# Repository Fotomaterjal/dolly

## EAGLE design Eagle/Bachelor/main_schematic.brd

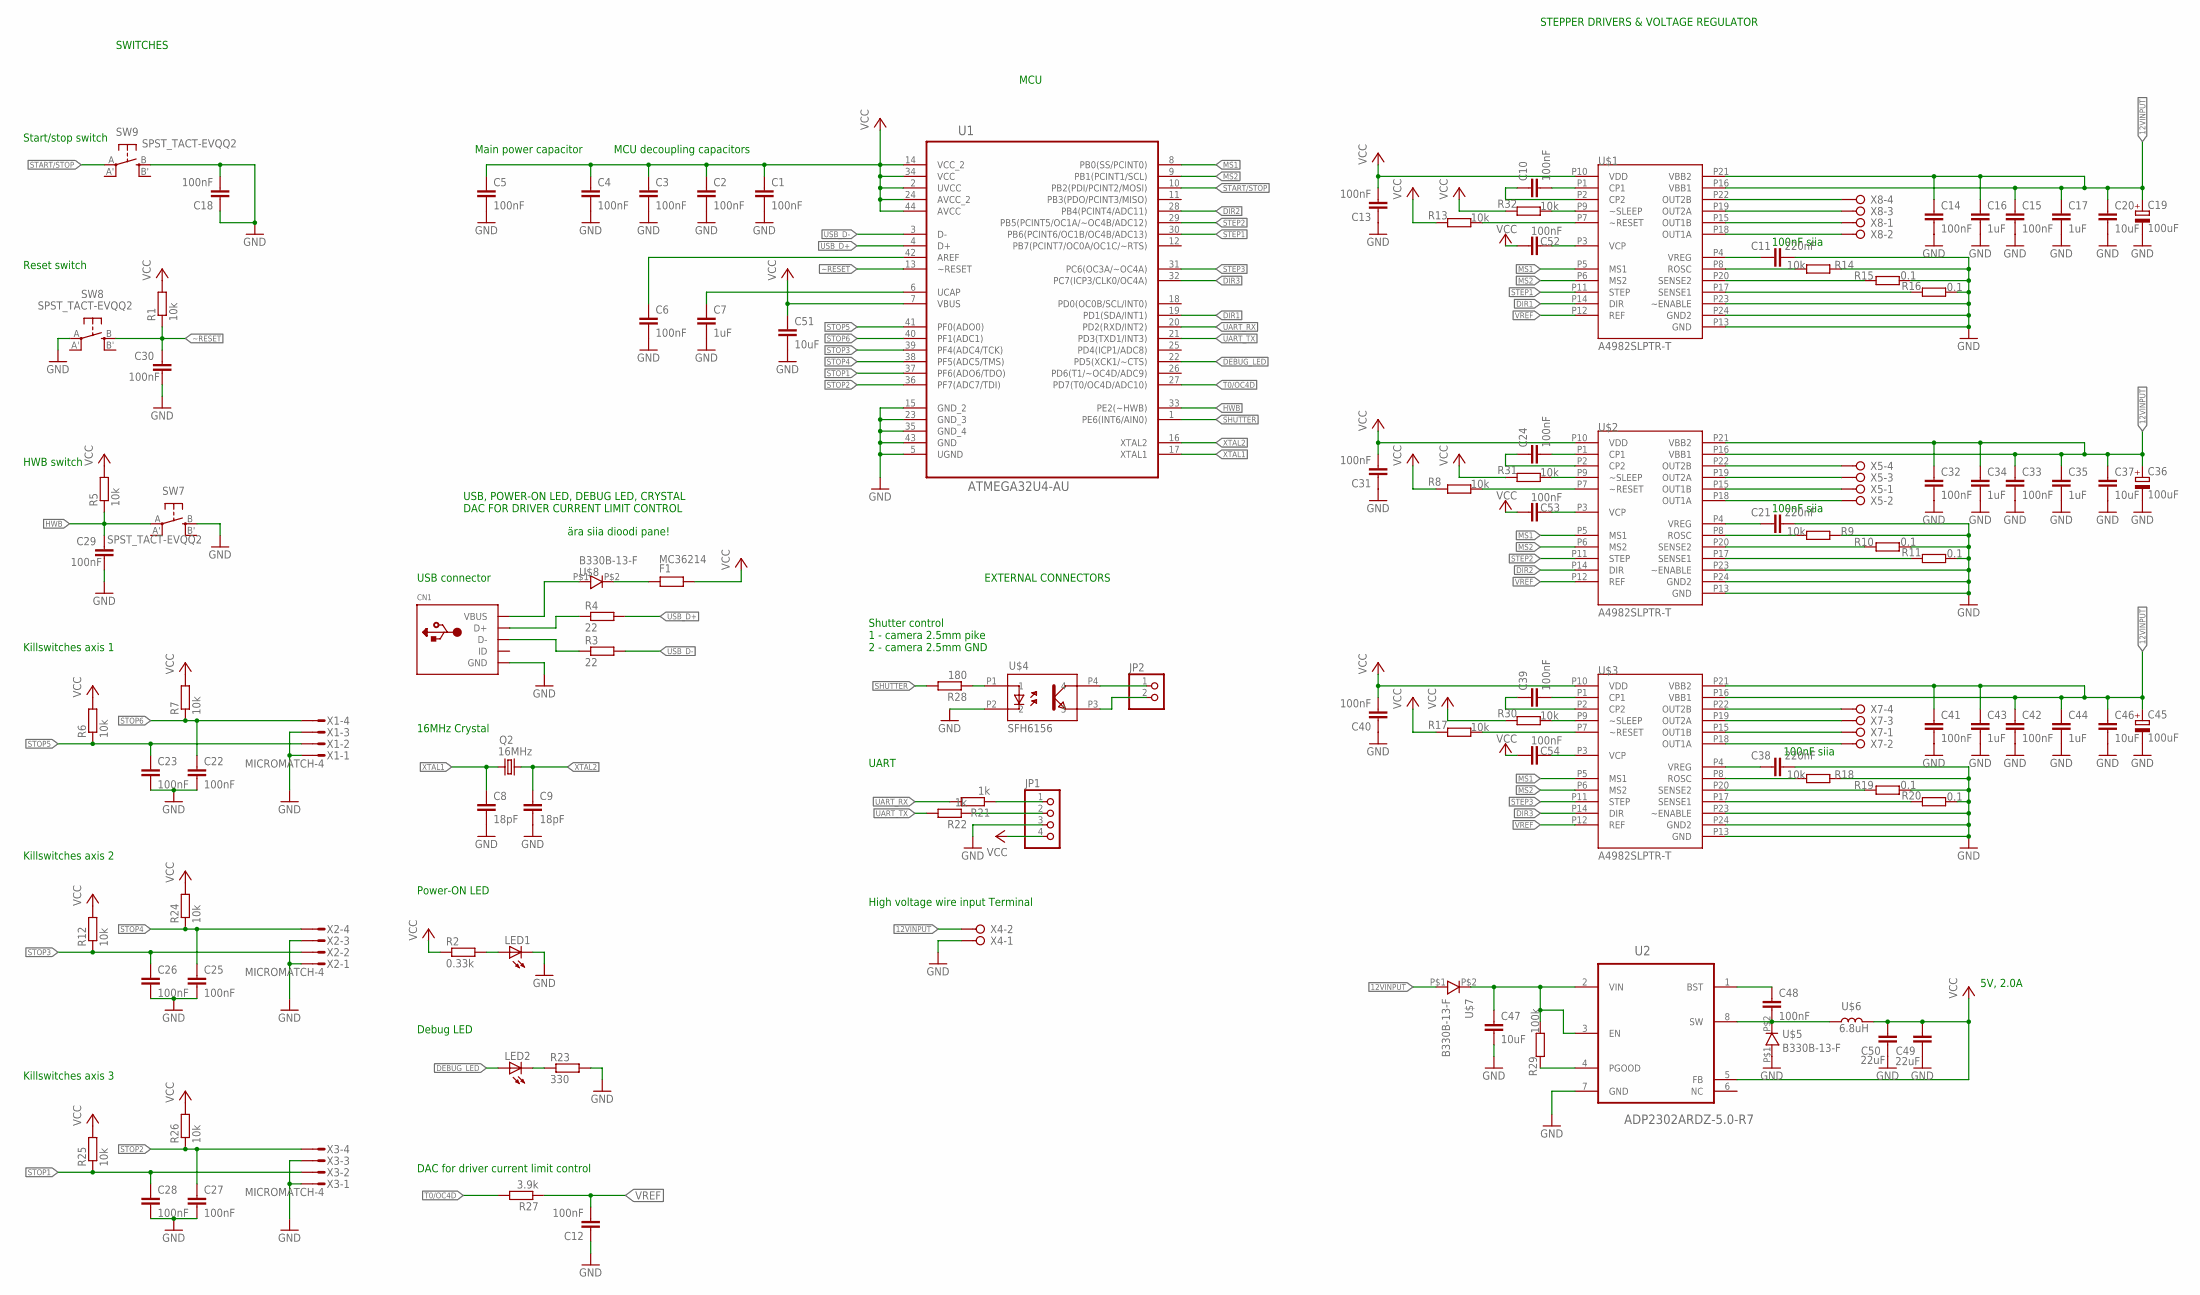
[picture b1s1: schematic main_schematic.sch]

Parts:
C1, C2, C3, C4, C5, C6, C10, C12, C13, C14, C15, C18, C22, C23, C24, C25, C26, C27, C28, C29, C30, C31, C32, C33, C39, C40, C41, C42, C52, C53, C54: 100nF; C0603K
C7, C16, C17, C34, C35, C43, C44: 1uF; C0603K
C8, C9: 18pF; C0603K
C11, C21, C38: 220nF; C0603K
C19, C36, C45: 100uF; E/7260-38R
C20, C37, C46, C47: 10uF; C1206K
C48: 100nF; C1206K
C49, C50: 22uF; C1206K
C51: 10uF; C0805
CN1: USBMINIB; USB-MINIB
F1: MC36214
JP1: PINHD-1X4; 1X04
JP2: PINHD-1X2; 1X02
LED1, LED2: LEDCHIP-LED0603; CHIP-LED0603
Q2: 16MHz; SM49
R1, R5, R6, R7, R8, R9, R12, R13, R14, R17, R18, R24, R25, R26, R30, R31, R32: 10k; R0603
R2: 0.33k; R0603
R3, R4: 22; R0603
R10, R11, R15, R16, R19, R20: 0.1; R0805
R21, R22: 1k; R0603
R23: 330; R0603
R27: 3.9k; R0603
R28: 180; R0603
R29: 100k; R0603
SW7, SW8, SW9: SPST_TACT-EVQQ2; EVQ-Q2
U1: ATMEGA32U4-AU; QFP80P1200X1200X120-44N
U2: ADP2302ARDZ-5.0-R7; SOIC127P600X175-9N
U$1, U$2, U$3: A4982SLPTR-T; TSSOP_24
U$4: SFH6156; SFH6165
U$5, U$7, U$8: B330B-13-F
U$6: 6.8uH; VLF10040
X1, X2, X3: MICROMATCH-4
X4: W237-02P; W237-132
X5, X7, X8: W237-04P; W237-4P

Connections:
12VINPUT: C14.1, C15.1, C16.1, C17.1, C19.+, C20.1, C32.1, C33.1, C34.1, C35.1, C36.+, C37.1, C41.1, C42.1, C43.1, C44.1, C45.+, C46.1, U$1.P16 (VBB1), U$1.P21 (VBB2), U$2.P16 (VBB1), U$2.P21 (VBB2), U$3.P16 (VBB1), U$3.P21 (VBB2), U$7.P$1, X4.2
DEBUG_LED: LED2.A, U1.22 (PD5(XCK1/~CTS))
DIR1: U1.19 (PD1(SDA/INT1)), U$1.P14 (DIR)
DIR2: U1.28 (PB4(PCINT4/ADC11)), U$2.P14 (DIR)
DIR3: U1.32 (PC7(ICP3/CLK0/OC4A)), U$3.P14 (DIR)
GND: C1.2, C2.2, C3.2, C4.2, C5.2, C6.2, C7.2, C8.2, C9.2, C11.1, C12.1, C13.1, C14.2, C15.2, C16.2, C17.2, C18.1, C18.2, C19.-, C20.2, C21.1, C22.2, C23.2, C25.2, C26.2, C27.2, C28.2, C29.2, C30.2, C31.1, C32.2, C33.2, C34.2, C35.2, C36.-, C37.2, C38.1, C40.1, C41.2, C42.2, C43.2, C44.2, C45.-, C46.2, C47.2, C49.1, C50.1, C51.2, CN1.GND, JP1.3, LED1.C, R9.1, R10.2, R11.2, R14.1, R15.2, R16.2, R18.1, R19.2, R20.2, R23.2, SW7.B (S), SW8.A, SW9.B (S), U1.5 (UGND), U1.15 (GND_2), U1.23 (GND_3), U1.35 (GND_4), U1.43 (GND), U2.7 (GND), U$1.P13 (GND), U$1.P23 (~ENABLE), U$1.P24 (GND2), U$2.P13 (GND), U$2.P23 (~ENABLE), U$2.P24 (GND2), U$3.P13 (GND), U$3.P23 (~ENABLE), U$3.P24 (GND2), U$4.P2 (2), U$5.P$1, X1.1, X1.3, X2.1, X2.3, X3.1, X3.3, X4.1
HIGH_VOLTAEG: C47.1, R29.2, U2.2 (VIN), U2.3 (EN), U$7.P$2
HWB: C29.1, R5.1, SW7.A, U1.33 (PE2(~HWB))
MS1: U1.8 (PB0(SS/PCINT0)), U$1.P5 (MS1), U$2.P5 (MS1), U$3.P5 (MS1)
MS2: U1.9 (PB1(PCINT1/SCL)), U$1.P6 (MS2), U$2.P6 (MS2), U$3.P6 (MS2)
unnamed: JP2.1, U$4.P4 (4)
unnamed: C6.1, U1.42 (AREF)
unnamed: LED1.A, R2.2
unnamed: CN1.D-, R3.1
unnamed: CN1.D+, R4.1
unnamed: C10.2, U$1.P1 (CP1)
unnamed: C10.1, U$1.P2 (CP2)
unnamed: U$1.P15 (OUT1B), X8.1
unnamed: U$1.P22 (OUT2B), X8.4
unnamed: C11.2, U$1.P4 (VREG)
unnamed: C7.1, U1.6 (UCAP)
unnamed: R13.2, U$1.P7 (~RESET)
unnamed: C24.2, U$2.P1 (CP1)
unnamed: R14.2, U$1.P8 (ROSC)
unnamed: R15.1, U$1.P20 (SENSE2)
unnamed: R16.1, U$1.P17 (SENSE1)
unnamed: C24.1, U$2.P2 (CP2)
unnamed: U$1.P19 (OUT2A), X8.3
unnamed: R10.1, U$2.P20 (SENSE2)
unnamed: U$1.P18 (OUT1A), X8.2
unnamed: R11.1, U$2.P17 (SENSE1)
unnamed: U$2.P22 (OUT2B), X5.4
unnamed: U$2.P15 (OUT1B), X5.1
unnamed: U$2.P19 (OUT2A), X5.3
unnamed: U$2.P18 (OUT1A), X5.2
unnamed: C21.2, U$2.P4 (VREG)
unnamed: R8.2, U$2.P7 (~RESET)
unnamed: R9.2, U$2.P8 (ROSC)
unnamed: C39.2, U$3.P1 (CP1)
unnamed: C39.1, U$3.P2 (CP2)
unnamed: R19.1, U$3.P20 (SENSE2)
unnamed: R20.1, U$3.P17 (SENSE1)
unnamed: U$3.P22 (OUT2B), X7.4
unnamed: U$3.P15 (OUT1B), X7.1
unnamed: U$3.P19 (OUT2A), X7.3
unnamed: U$3.P18 (OUT1A), X7.2
unnamed: C38.2, U$3.P4 (VREG)
unnamed: R17.2, U$3.P7 (~RESET)
unnamed: CN1.VBUS, U$8.P$1
unnamed: JP1.1, R21.1
unnamed: JP1.2, R22.1
unnamed: JP2.2, U$4.P3 (3)
unnamed: R18.2, U$3.P8 (ROSC)
unnamed: LED2.C, R23.1
unnamed: R29.1, U2.4 (PGOOD)
unnamed: C48.1, U2.1 (BST)
unnamed: R28.1, U$4.P1 (1)
unnamed: F1.P$1, U$8.P$2
unnamed: C52.1, U$1.P3 (VCP)
unnamed: C48.2, U2.8 (SW), U$5.P$2, U$6.P$2
unnamed: C53.1, U$2.P3 (VCP)
unnamed: C54.1, U$3.P3 (VCP)
unnamed: R30.2, U$3.P9 (~SLEEP)
unnamed: R31.2, U$2.P9 (~SLEEP)
unnamed: R32.2, U$1.P9 (~SLEEP)
SHUTTER: R28.2, U1.1 (PE6(INT6/AIN0))
START/STOP: SW9.A, U1.10 (PB2(PDI/PCINT2/MOSI))
STEP1: U1.30 (PB6(PCINT6/OC1B/OC4B/ADC13)), U$1.P11 (STEP)
STEP2: U1.29 (PB5(PCINT5/OC1A/~OC4B/ADC12)), U$2.P11 (STEP)
STEP3: U1.31 (PC6(OC3A/~OC4A)), U$3.P11 (STEP)
STOP1: C28.1, R25.1, U1.37 (PF6(ADO6/TDO)), X3.2
STOP2: C27.1, R26.1, U1.36 (PF7(ADC7/TDI)), X3.4
STOP3: C26.1, R12.1, U1.39 (PF4(ADC4/TCK)), X2.2
STOP4: C25.1, R24.1, U1.38 (PF5(ADC5/TMS)), X2.4
STOP5: C23.1, R6.1, U1.41 (PF0(ADO0)), X1.2
STOP6: C22.1, R7.1, U1.40 (PF1(ADC1)), X1.4
T0/OC4D: R27.2, U1.27 (PD7(T0/OC4D/ADC10))
UART_RX: R21.2, U1.20 (PD2(RXD/INT2))
UART_TX: R22.2, U1.21 (PD3(TXD1/INT3))
USB_D+: R4.2, U1.4 (D+)
USB_D-: R3.2, U1.3 (D-)
VCC: C1.1, C2.1, C3.1, C4.1, C5.1, C13.2, C31.2, C40.2, C49.2, C50.2, C51.1, C52.2, C53.2, C54.2, F1.P$2, JP1.4, R1.2, R2.1, R5.2, R6.2, R7.2, R8.1, R12.2, R13.1, R17.1, R24.2, R25.2, R26.2, R30.1, R31.1, R32.1, U1.2 (UVCC), U1.7 (VBUS), U1.14 (VCC_2), U1.24 (AVCC_2), U1.34 (VCC), U1.44 (AVCC), U2.5 (FB), U$1.P10 (VDD), U$2.P10 (VDD), U$3.P10 (VDD), U$6.P$1
VREF: C12.2, R27.1, U$1.P12 (REF), U$2.P12 (REF), U$3.P12 (REF)
XTAL1: C8.1, Q2.1, U1.17 (XTAL1)
XTAL2: C9.1, Q2.2, U1.16 (XTAL2)
~RESET: C30.1, R1.1, SW8.B (S), U1.13 (~RESET)

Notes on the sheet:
MCU decoupling capacitors
Main power capacitor
Reset switch
Power-ON LED
USB connector
HWB switch
Start/stop switch
Killswitches axis 1
Killswitches axis 2
Killswitches axis 3
Debug LED
16MHz Crystal
Shutter control 1 - camera 2.5mm pike 2 - camera 2.5mm GND
DAC for driver current limit control
UART
High voltage wire input Terminal
5V, 2.0A
SWITCHES
MCU
USB, POWER-ON LED, DEBUG LED, CRYSTAL DAC FOR DRIVER CURRENT LIMIT CONTROL
STEPPER DRIVERS & VOLTAGE REGULATOR
EXTERNAL CONNECTORS
ära siia dioodi pane!
100nF siia

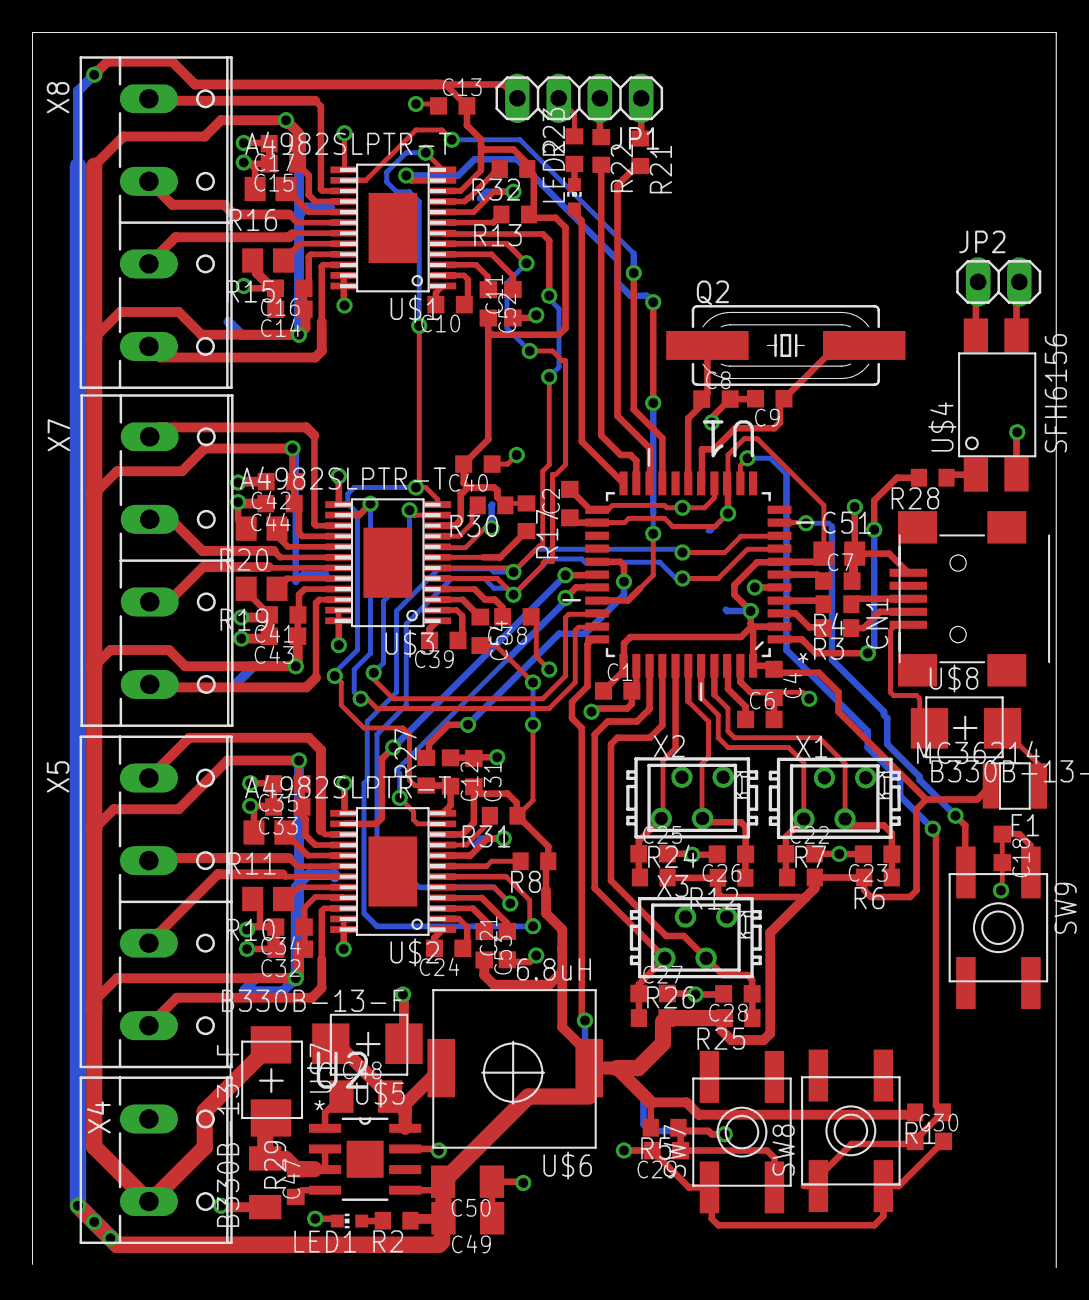
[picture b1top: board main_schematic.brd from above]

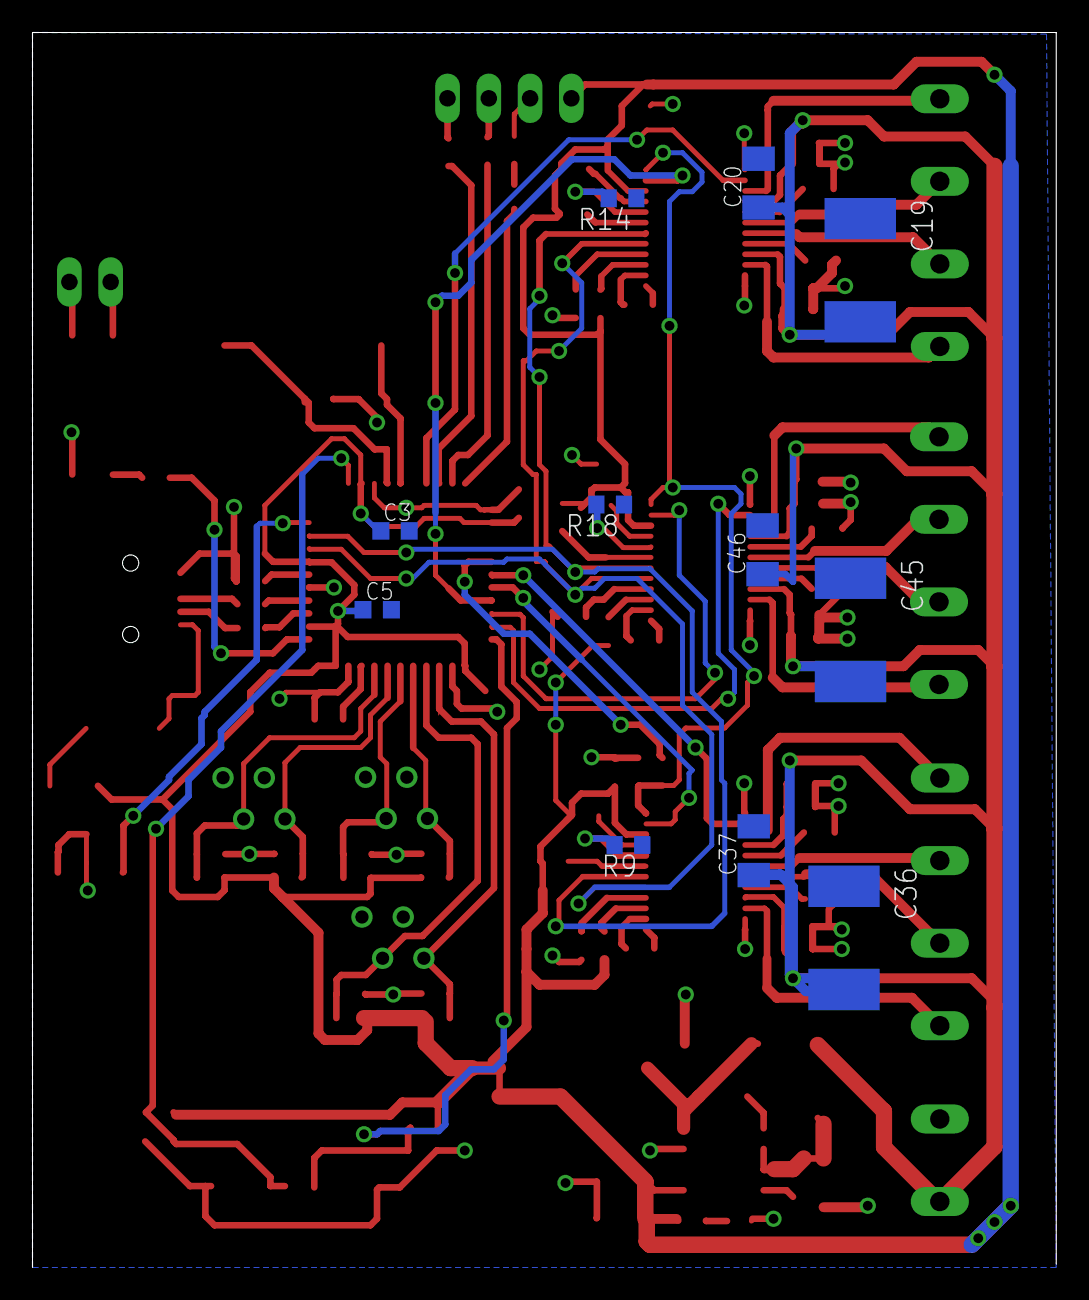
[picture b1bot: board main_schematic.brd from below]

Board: 2 copper layers, 63.0 x 76.0 mm, 113 parts (11 on the bottom side), 86 nets.

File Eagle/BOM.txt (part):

Partlist exported from C:/Users/Oll/Dropbox/2014kool/Lõputöö/Eagle/Bachelor/main_schematic.sch at 2.12.2014 10:23:13

Part Value              Device              Package                 Description                                             MF MPN                OC_FARNELL OC_NEWARK PACKAGE SUPPLIER      
C1   100nF              C-EUC0603K          C0603K                  CAPACITOR, European symbol                                                                                               
C2   100nF              C-EUC0603K          C0603K                  CAPACITOR, European symbol                                                                                               
C3   100nF              C-EUC0603K          C0603K                  CAPACITOR, European symbol                                                                                               
C4   100nF              C-EUC0603K          C0603K                  CAPACITOR, European symbol                                                                                               
C5   100nF              C-EUC0603K          C0603K                  CAPACITOR, European symbol                                                                                               
C6   100nF              C-EUC0603K          C0603K                  CAPACITOR, European symbol                                                                                               
C7   1uF                C-EUC0603K          C0603K                  CAPACITOR, European symbol                                                                                               
C8   18pF               C-EUC0603K          C0603K                  CAPACITOR, European symbol                                                                                               
C9   18pF               C-EUC0603K          C0603K                  CAPACITOR, European symbol                                                                                               
C10  100nF              C-EUC0603K          C0603K                  CAPACITOR, European symbol                                                                                               
C11  220nF              C-EUC0603K          C0603K                  CAPACITOR, European symbol                                                                                               
C12  100nF              C-EUC0603K          C0603K                  CAPACITOR, European symbol                                                                                               
C13  100nF              C-EUC0603K          C0603K                  CAPACITOR, European symbol                                                                                               
C14  100nF              C-EUC0603K          C0603K                  CAPACITOR, European symbol                                                                                               
C15  100nF              C-EUC0603K          C0603K                  CAPACITOR, European symbol                                                                                               
C16  1uF                C-EUC0603K          C0603K                  CAPACITOR, European symbol                                                                                               
C17  1uF                C-EUC0603K          C0603K                  CAPACITOR, European symbol                                                                                               
C18  100nF              C-EUC0603K          C0603K                  CAPACITOR, European symbol                                                                                               
C19  100uF              CPOL-EUE/7260-38R   E/7260-38R              POLARIZED CAPACITOR, European symbol                                                                                     
C20  10uF               C-EUC1206K          C1206K                  CAPACITOR, European symbol                                                                                               
C21  220nF              C-EUC0603K          C0603K                  CAPACITOR, European symbol                                                                                               
C22  100nF              C-EUC0603K          C0603K                  CAPACITOR, European symbol                                                                                               
C23  100nF              C-EUC0603K          C0603K                  CAPACITOR, European symbol                                                                                               
C24  100nF              C-EUC0603K          C0603K                  CAPACITOR, European symbol                                                                                               
C25  100nF              C-EUC0603K          C0603K                  CAPACITOR, European symbol                                                                                               
C26  100nF              C-EUC0603K          C0603K                  CAPACITOR, European symbol                                                                                               
C27  100nF              C-EUC0603K          C0603K                  CAPACITOR, European symbol                                                                                               
C28  100nF              C-EUC0603K          C0603K                  CAPACITOR, European symbol                                                                                               
C29  100nF              C-EUC0603K          C0603K                  CAPACITOR, European symbol                                                                                               
C30  100nF              C-EUC0603K          C0603K                  CAPACITOR, European symbol                                                                                               
C31  100nF              C-EUC0603K          C0603K                  CAPACITOR, European symbol                                                                                               
C32  100nF              C-EUC0603K          C0603K                  CAPACITOR, European symbol                                                                                               
C33  100nF              C-EUC0603K          C0603K                  CAPACITOR, European symbol                                                                                               
C34  1uF                C-EUC0603K          C0603K                  CAPACITOR, European symbol                                                                                               
C35  1uF                C-EUC0603K          C0603K                  CAPACITOR, European symbol                                                                                               
C36  100uF              CPOL-EUE/7260-38R   E/7260-38R              POLARIZED CAPACITOR, European symbol                                                                                     
C37  10uF               C-EUC1206K          C1206K                  CAPACITOR, European symbol                                                                                               
C38  220nF              C-EUC0603K          C0603K                  CAPACITOR, European symbol                                                                                               
C39  100nF              C-EUC0603K          C0603K                  CAPACITOR, European symbol                                                                                               
C40  100nF              C-EUC0603K          C0603K                  CAPACITOR, European symbol                                                                                               
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
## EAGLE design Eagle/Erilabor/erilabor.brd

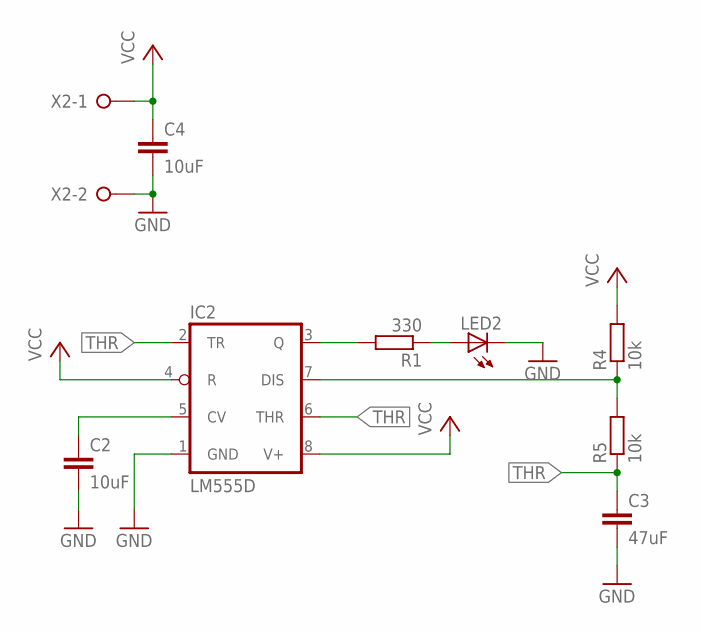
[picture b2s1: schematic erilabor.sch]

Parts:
C2, C4: 10uF; C0805K
C3: 47uF; C1210K
IC2: LM555D; SO08
LED2: LEDCHIP-LED0603; CHIP-LED0603
R1: 330; R0603
R4, R5: 10k; R0603
X2: W237-2N

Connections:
GND: C2.2, C3.2, C4.2, IC2.1 (GND), LED2.C, X2.2
unnamed: IC2.3 (Q), R1.2
unnamed: LED2.A, R1.1
unnamed: C2.1, IC2.5 (CV)
unnamed: IC2.7 (DIS), R4.1, R5.2
THR: C3.1, IC2.2 (TR), IC2.6 (THR), R5.1
VCC: C4.1, IC2.4 (R), IC2.8 (V+), R4.2, X2.1

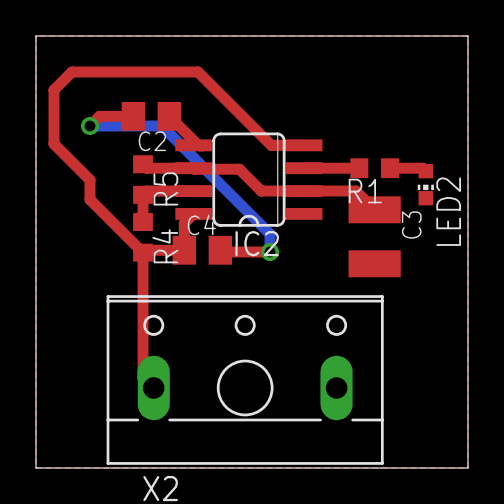
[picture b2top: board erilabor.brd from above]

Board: 2 copper layers, 24.0 x 24.0 mm, 9 parts (0 on the bottom side), 7 nets.

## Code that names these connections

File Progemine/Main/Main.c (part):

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	rmCLKDIV8();
	////////////// Blinking LED freq ///////////////////////////
	//int led = 0x20;
	DDRD |= (1<<PD5);	
	//DDRF |= (1<<PORTF7 | 1<<PORTF6);	// 
	PORTD = PORTD^(1<<PD5);	// invert LED value
	//if((~PINF)&(1 << PF7)){
		//////PORTD |= (1<<PD5);
		//PORTD &= ~(1<<PD5);
		//////PORTD = PORTD^(1<<PD5);	// invert LED value
		//////}else{
		//////PORTD &= ~(1<<PD5);
	//}
	
	//for(int i = 0; i<100000; i++){
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	init_UART();				// settings and RX TX enable stuff
	///////////// Main loop //////////////////////////////	
	while(1){
		//PORTD |= (1<<PD5);
		//while(1){
			//while(!PINF7){
				//PORTD &= ~(1<<PD5);
			//}
			//while(PINF & (1<<PINF7)){
				//PORTD |= (1<<PD5);
			//}	
		//}

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void changeDistDir(uint8_t dir){
	if(dir){
		// Change upper stepper DIR to FORWARD movement
		PORTD |= (1 << PD1);
		distDirFlag = 1;
	}else{
		// Change upper stepper DIR to BACKWARDS movement
		PORTD &= ~(1 << PD1);
		distDirFlag = 0;
	}	
}
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void changeHorRotDir(uint8_t dir){
	if(dir){
		// Change middle stepper DIR to FORWARD movement
		PORTC |= (1 << PC7);
		horDirFlag = 1;
	}else{
		// Change middle stepper DIR to BACKWARDS movement
		PORTC &= ~(1 << PC7);
		horDirFlag = 0;
	}
}
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void changeVerRotDir(uint8_t dir){
	if(dir){
		// Change upper stepper DIR to FORWARD movement
		PORTB |= (1 << PB4);
		//PORTB &= ~(1 << PB4);
		verDirFlag = 1;
	}else{
		// Change upper stepper DIR to BACKWARDS movement
		PORTB &= ~(1 << PB4);
		//PORTB |= (1 << PB4);
		verDirFlag = 0;
	}
}
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// I_tripMax = V_ref/(8*R_s), R_s = 0.1 Ohm
// 200 mA = V_ref/0.8 -> V_ref = 0.16V = 3.2% uptime -> OCR4D = 8
void setCurrentLimiter_T4(int ocr_value){
	DDRD |= (1<<PD7);					//OCR4D to output
	OCR4D = ocr_value;					// set count limit
	TCCR4C |= (1<<COM4D1)|(1<<PWM4D);	// set fast PWM mode - clear on CM, enable PWM @ OCR4D
	TCCR4B |= (1<<CS40);				// set CPU clock for timer clock
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
//Initialize stepper motor outputs (step&direction&mode)
void init_steppers(){
	// STEP2 (bottom stepper) is PB5
	DDRB |= (1 << PB5);
	// DIR2
	DDRB |= (1 << PB4);
	PORTB |= (1 << PB4);
	
	// STEP3 (middle stepper) is PC6
	DDRC |= (1 << PC6);
	// DIR3 middle (distance) stepper
	DDRC |= (1 << PC7);
	PORTC |= (1 << PC7);
	
	// STEP1 (upper stepper) is PB6
	DDRB |= (1 << PB6);
	// DIR1 upper (distance) stepper
	DDRD |= (1 << PD1);
	PORTD |= (1 << PD1);
		
	//// Change step mode
	DDRB |= (1 << PB0) | (1 << PB1);
	PORTB |= (1 << PB0) | (1 << PB1);
}

///////////////////////////////////////////////// STEP INTERRUPTS /////////////////////////////////////////////
// Upper (distance) stepper interrupt
SIGNAL(TIMER1_COMPA_vect){
    //Step on step2 (PB5), upper stepper
    //TEST WITH POWER SUPPLY      
	if(distTimerTOCounterFlag){
		if(distTimerTOCounter < (distTimerTOCounterMax-1)){
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			// step on that, man
			if(distDirFlag && (PINF & (1<<PINF1))){
				//not touching end position but moving forward
				PORTB = PORTB^(1<<PB6);
				PORTB = PORTB^(1<<PB6);
				PORTD |= (1<<PD5);
				} else if(!distDirFlag && (PINF & (1<<PINF0))){
				//not touching start position and moving backward
				PORTB = PORTB^(1<<PB6);
				PORTB = PORTB^(1<<PB6);
				PORTD |= (1<<PD5);
				}else{
				PORTD &= ~(1<<PD5);
			}
			// where am I going?
			if(distDirFlag){
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		// step on that, man. not using preScalers, man
		if(distDirFlag && (PINF & (1<<PINF1))){
			//not touching end position but moving forward
			PORTB = PORTB^(1<<PB6);
			PORTB = PORTB^(1<<PB6);
			PORTD |= (1<<PD5);
		} else if(!distDirFlag && (PINF & (1<<PINF0))){
			//not touching start position and moving backward
			PORTB = PORTB^(1<<PB6);
			PORTB = PORTB^(1<<PB6);
			PORTD |= (1<<PD5);
		}else{
			PORTD &= ~(1<<PD5);
		}
		
		// where am I going?
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// Middle (horizontal rotation) stepper
SIGNAL(TIMER3_COMPA_vect){
	//TEST WITHH POWER SUPPLY
	//PC6 = STEP3
	//PORTD = PORTD^(1<<PD5);	// invert LED value	
    //Step on step2 (PB5), upper stepper
    //TEST WITH POWER SUPPLY
    if(horTimerTOCounterFlag){
	    if(horTimerTOCounter < (horTimerTOCounterMax-1)){
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		}else{
		    horTimerTOCounter = 0;
		    // step on that, man
		    PORTC = PORTC^(1<<PC6);
		    PORTC = PORTC^(1<<PC6);
		    // where am I going?
		    if(horDirFlag){
			    curHorDeg++;
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	    }
	}else{
	    // step on that, man. not using preScalers, man
	    PORTC = PORTC^(1<<PC6);
	    PORTC = PORTC^(1<<PC6);
	    // where am I going?
	    if(horDirFlag){
		    curHorDeg++;
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			verTimerTOCounter = 0;
			// do the stepping action
			//TEST WITH POWER SUPPLY
			//PB5 = STEP2
			PORTB = PORTB^(1<<PB5);
			PORTB = PORTB^(1<<PB5);
			if(verDirFlag){
				curVerDeg ++;
			}else{
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	}else{
		// do the stepping action
		//TEST WITH POWER SUPPLY
		//PB5 = STEP2
		PORTB = PORTB^(1<<PB5);
		PORTB = PORTB^(1<<PB5);
		if(verDirFlag){
			curVerDeg ++;
		}else{
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
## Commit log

2015-01-03 Esimene push kogu töökaustale
2015-01-19 Lisandus uus kaust "progemine" muutsin juurkausta nime flipile arusaadavamaks
2015-01-29 Tehtud solidworksi ja progemist
2015-02-10 Igaks juhuks
2015-02-11 Kõik progemine seni
2015-02-12 Cleaned up the main code. I hope I didn't brake anything.
2015-02-21 USART receive 16 bit numbers working now. If you start your USART transmission with byte 'k' then the next 4 16-bit numbers will be saved into inner keyframe list as a keyframe object.
2015-02-21 Fixed USART multiple byte receive corruption problem. Now can receive many keyframes at one time.
2015-02-24 Code now changes Timer 1A compare match frequency depending on the USART receive vector. Aka code ready for receiving bluetooth signals for testing.
2015-03-06 conBT.write(asi); works and sending bytes to board!
2015-03-11 It is working but messing up the order of the received keyframes. Gonna try to fix this thing with sending extra order number from android app.
2015-03-11 Keyframe intake from Bluetooth working perfectly!
2015-03-20 Solidworks files before printing 20th march
2015-03-24 Added all three stepper support and movement.
2015-04-08 A lot of stuff done Preparing to cut and print most of the stuff
2015-04-08 Most of the stuff done, but have errors Error in android, nullpointerexception Verrotate and horrotate not working correctly
2015-04-21 Put onto microstepping mode. Everything working, steps working, keyframes working, backwards stepping working. Now Have to calibrate to work as slowly as needed and as fast as needed. Looking good (Y)
2015-04-26 All the timers seem to be working. A small problem with some numbers, for example travel 16 degrees in 3 seconds gives some problems on HorTimer somehow. Don't know the cause.
2015-04-29 Device moving working but ver thing still slower. Don't know the reason
2015-05-07 Changed uart not to use interrupts, seems to be working
2015-05-10 Everything in place but some screws missing
2015-05-23 Everything seems to be OK
2015-05-23 Seems to be working well (Y)
2015-06-13 Done
2016-03-24 Testing what changes have been made
